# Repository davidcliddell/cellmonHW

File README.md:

# cellmonHW
HW for very small Lithium cell monitor using attiny85

Associated repros  
cellmonFW - firmware for the cell monitor. Design info (HW and FW) in the design.h file  
cellmonISPHW - schematic for a programmer and test harness based on Arduino UNO  
cellmonISPFW - firmware for above. Programs the attiny85 and tests cellmon, based on ArduinoISP code  
Coming soon  
BMSHW - an ESP32 based BMS using Hat Labs (hatlabs.fi) SH-ESP32  
BMSFW - Firmware for above BMS

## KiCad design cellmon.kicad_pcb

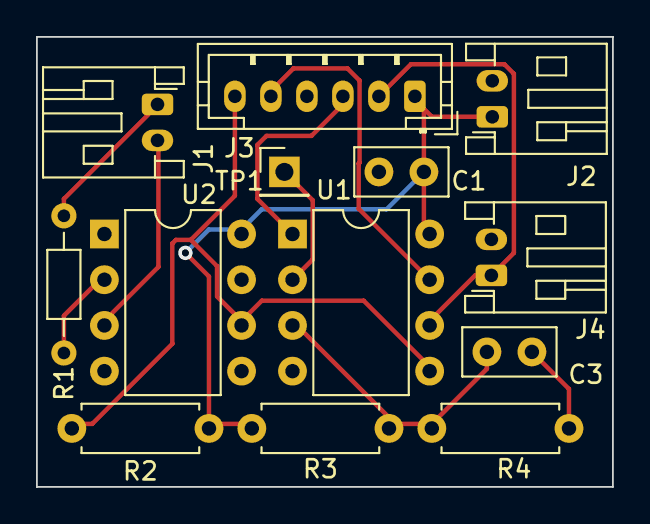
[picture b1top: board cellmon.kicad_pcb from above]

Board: 2 copper layers, 32.0 x 25.0 mm, 13 parts (0 on the bottom side), 11 nets.

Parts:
C1: 10uF; C_Disc_D5.0mm_W2.5mm_P2.50mm
C3: 100nF; C_Disc_D5.0mm_W2.5mm_P2.50mm
J1, J2, J4: Conn_01x02_Male; JST_PH_S2B-PH-K_1x02_P2.00mm_Horizontal
J3: Conn_01x06; JST_PH_B6B-PH-K_1x06_P2.00mm_Vertical
R1: 2K2; R_Axial_DIN0204_L3.6mm_D1.6mm_P7.62mm_Horizontal
R2: 10K; R_Axial_DIN0207_L6.3mm_D2.5mm_P7.62mm_Horizontal
R3: 33K 1%; R_Axial_DIN0207_L6.3mm_D2.5mm_P7.62mm_Horizontal
R4: 10K 1%; R_Axial_DIN0207_L6.3mm_D2.5mm_P7.62mm_Horizontal
TP1: TestPoint; PinHeader_1x01_P2.54mm_Vertical
U1: ATtiny85V-10S; DIP-8_W7.62mm
U2: 6N136; DIP-8_W7.62mm

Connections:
/RST: J3.3, U1.1 (~RESET/PB5)
/Rx/MOSI: J3.6, R2.2, U1.5 (AREF/PB0), U2.6
/SCK: J3.5, U1.7 (PB2)
/Tx/MISO: J3.2, J4.1, U1.6 (PB1)
GND: C1.2, C3.2, J2.2, J3.4, J4.2, R4.2, U1.4 (GND), U2.5
unnamed: C3.1, R3.2, R4.1, U1.3 (XTAL2/PB4)
unnamed: J1.1, R1.1
unnamed: J1.2, U2.3
unnamed: R1.2, U2.2
unnamed: TP1.1, U1.2 (XTAL1/PB3)
VCC: C1.1, J2.1, J3.1, R2.1, R3.1, U1.8 (VCC), U2.8

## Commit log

2023-03-10 Update to R2 PCB
2023-03-10 R2 PCB
